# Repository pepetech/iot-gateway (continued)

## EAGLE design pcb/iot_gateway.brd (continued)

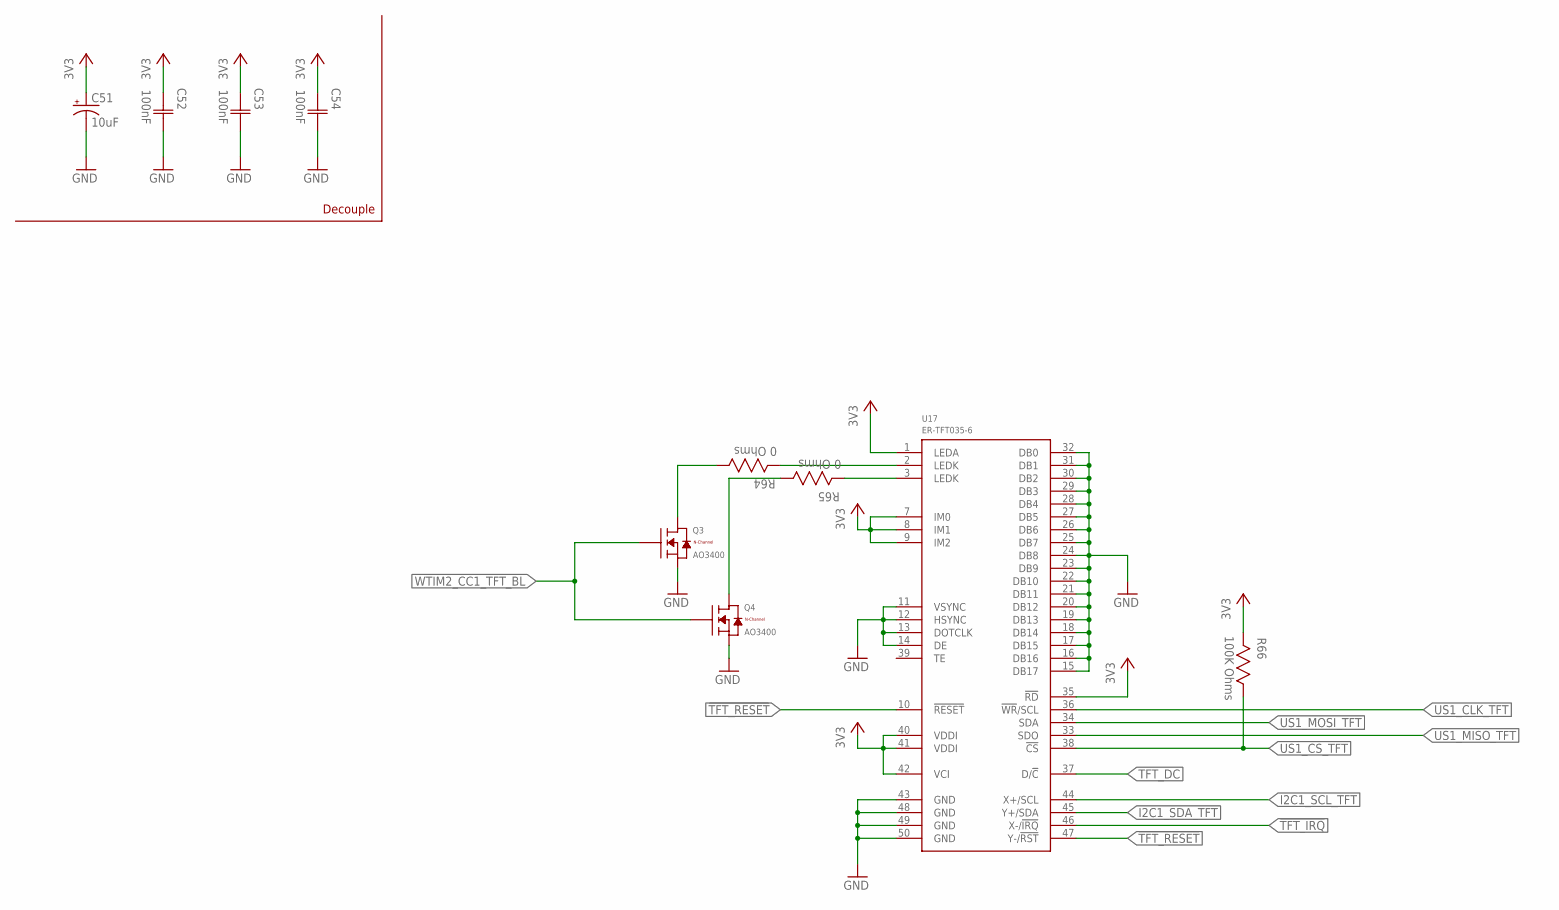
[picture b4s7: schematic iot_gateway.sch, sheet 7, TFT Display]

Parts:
C51: 10uF; TAN-CAP-CASE-A
C52, C53, C54: 100nF; CAP0603
Q3, Q4: AO3400; SOT23
R64, R65: 0 Ohms; RES0603
R66: 100K Ohms; RES0603
U17: ER-TFT035-6; ZIF50

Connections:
3V3: C51.A (+), C52.1 (C1), C53.1 (C1), C54.1 (C1), R66.2, U17.1 (LEDA), U17.7 (IM0), U17.8 (IM1), U17.9 (IM2), U17.35 (!RD), U17.40 (VDDI), U17.41 (VDDI), U17.42 (VCI); also elsewhere on the board
!TFT_IRQ: U17.46 (X-/!IRQ!); also elsewhere on the board
!TFT_RESET: U17.10 (!RESET), U17.47 (Y-/!RST!); also elsewhere on the board
GND: C51.C (-), C52.2 (C2), C53.2 (C2), C54.2 (C2), Q3.2 (S), Q4.2 (S), U17.11 (VSYNC), U17.12 (HSYNC), U17.13 (DOTCLK), U17.14 (DE), U17.15 (DB17), U17.16 (DB16), U17.17 (DB15), U17.18 (DB14), U17.19 (DB13), U17.20 (DB12), U17.21 (DB11), U17.22 (DB10), U17.23 (DB9), U17.24 (DB8), U17.25 (DB7), U17.26 (DB6), U17.27 (DB5), U17.28 (DB4), U17.29 (DB3), U17.30 (DB2), U17.31 (DB1), U17.32 (DB0), U17.43 (GND), U17.48 (GND), U17.49 (GND), U17.50 (GND); also elsewhere on the board
I2C1_SCL_TFT: U17.44 (X+/SCL); also elsewhere on the board
I2C1_SDA_TFT: U17.45 (Y+/SDA); also elsewhere on the board
unnamed: Q3.3 (D), R64.1
unnamed: Q4.3 (D), R65.1
unnamed: R65.2, U17.3 (LEDK)
unnamed: R64.2, U17.2 (LEDK)
TFT_DC: U17.37 (D/!C!); also elsewhere on the board
US1_CLK_TFT: U17.36 (!WR!/SCL); also elsewhere on the board
US1_CS_TFT: R66.1, U17.38 (!CS); also elsewhere on the board
US1_MISO_TFT: U17.33 (SDO); also elsewhere on the board
US1_MOSI_TFT: U17.34 (SDA); also elsewhere on the board
WTIM2_CC1_TFT_BL: Q3.1 (G), Q4.1 (G); also elsewhere on the board

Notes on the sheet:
Decouple

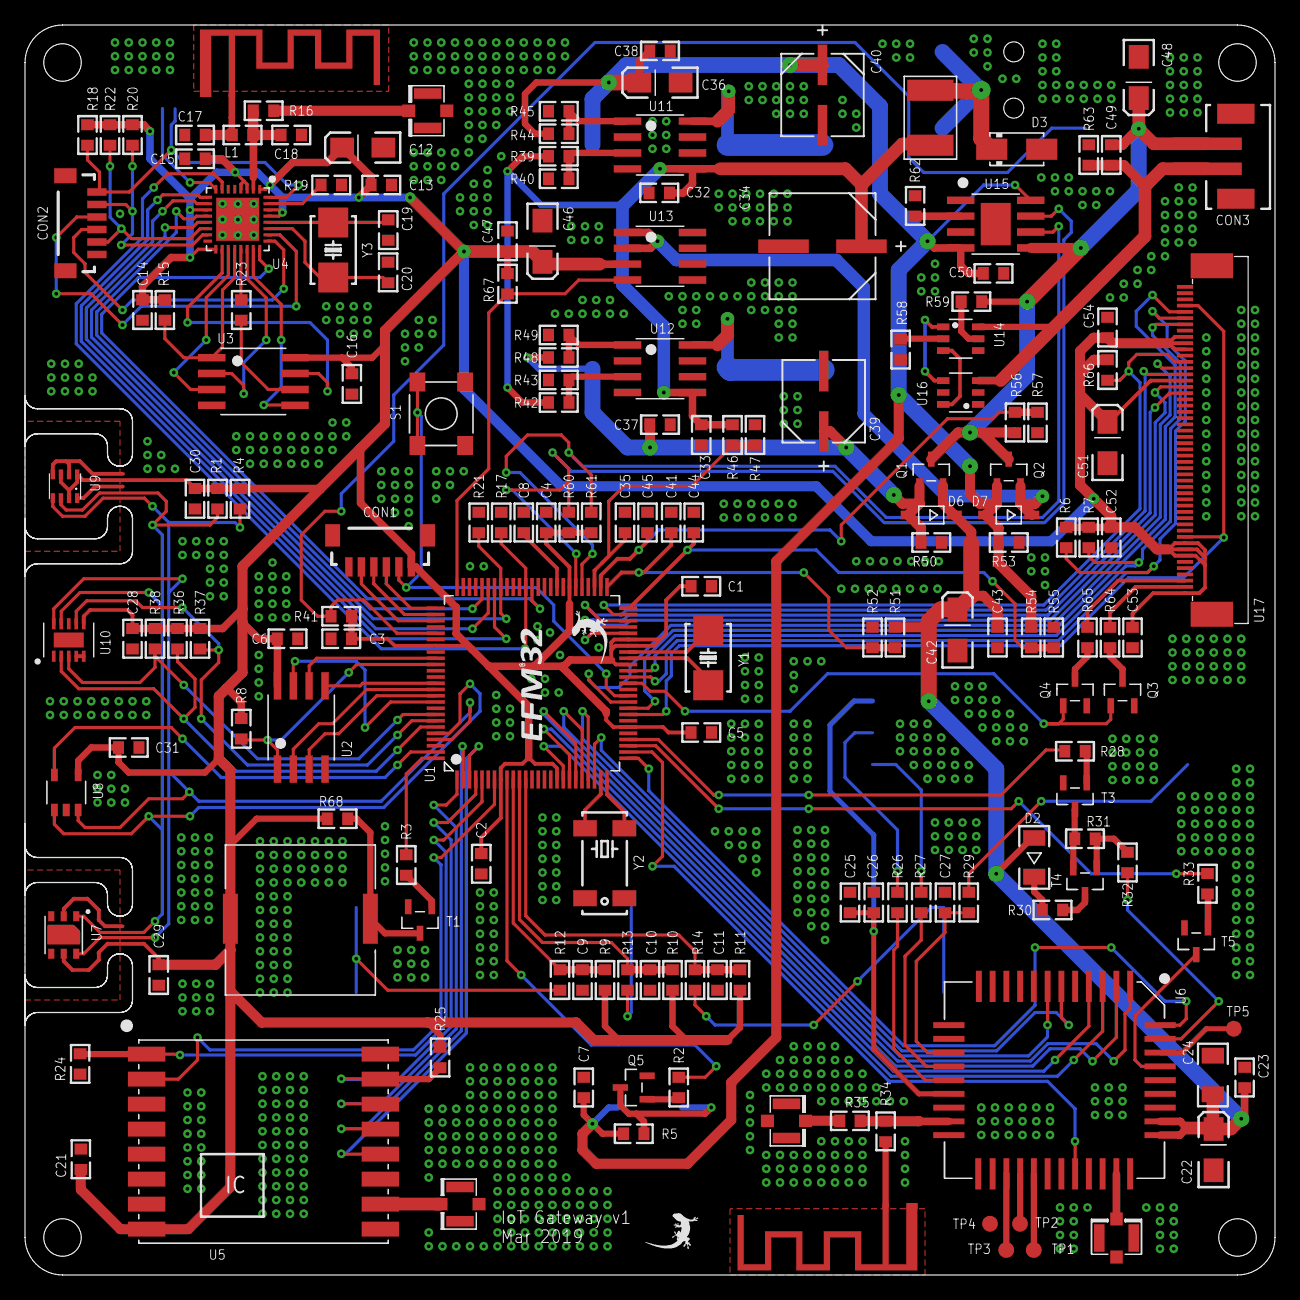
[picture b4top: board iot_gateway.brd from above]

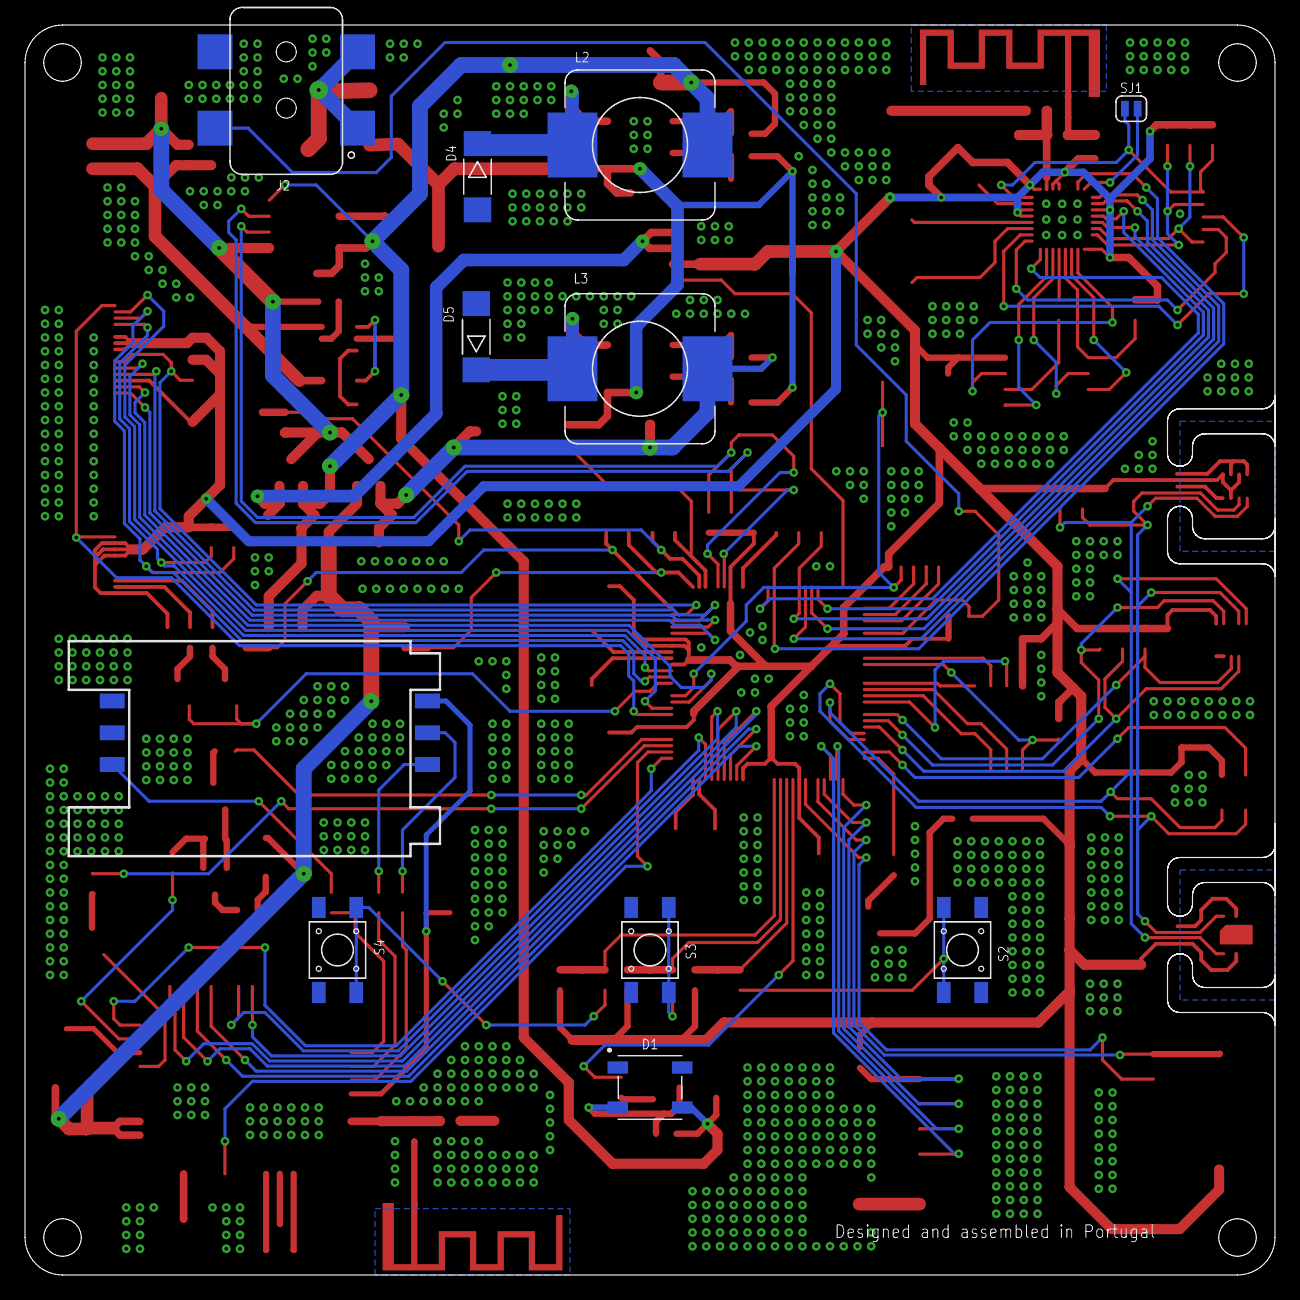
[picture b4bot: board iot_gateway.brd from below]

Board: 2 copper layers, 100.0 x 100.0 mm, 185 parts (11 on the bottom side), 142 nets.

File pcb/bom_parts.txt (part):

Partlist exported from E:/Projetos/ARM/ARMdev/projects/iot-gateway/pcb/iot_gateway.sch at 06/05/2019 23:54

Part   Value              Device                            Package                     Description                                                 
B1     BUZZER-SMD         BUZZER-SMD                        SMD                                                                                     
C1     100nF              CAPACITOR-0603                    CAP0603                                                                                 
C2     100nF              CAPACITOR-0603                    CAP0603                                                                                 
C3     100nF              CAPACITOR-0603                    CAP0603                                                                                 
C4     100nF              CAPACITOR-0603                    CAP0603                                                                                 
C5     100nF              CAPACITOR-0603                    CAP0603                                                                                 
C6     100nF              CAPACITOR-0603                    CAP0603                                                                                 
C7     100nF              CAPACITOR-0603                    CAP0603                                                                                 
C8     1uF                CAPACITOR-0603                    CAP0603                                                                                 
C9     1nF                CAPACITOR-0603                    CAP0603                                                                                 
C10    1nF                CAPACITOR-0603                    CAP0603                                                                                 
C11    1nF                CAPACITOR-0603                    CAP0603                                                                                 
C12    10uF               TANTALUM-CAPACITOR-CASE-A-EIA3216 TAN-CAP-CASE-A                                                                          
C13    100nF              CAPACITOR-0603                    CAP0603                                                                                 
C14    100nF              CAPACITOR-0603                    CAP0603                                                                                 
C15    100nF              CAPACITOR-0603                    CAP0603                                                                                 
C16    100nF              CAPACITOR-0603                    CAP0603                                                                                 
C17    4pF                CAPACITOR-0603                    CAP0603                                                                                 
C18    4.7pF              CAPACITOR-0603                    CAP0603                                                                                 
C19    20pF               CAPACITOR-0603                    CAP0603                                                                                 
C20    20pF               CAPACITOR-0603                    CAP0603                                                                                 
C21    100nF              CAPACITOR-0603                    CAP0603                                                                                 
C22    10uF               TANTALUM-CAPACITOR-CASE-A-EIA3216 TAN-CAP-CASE-A                                                                          
C23    100nF              CAPACITOR-0603                    CAP0603                                                                                 
C24    100uF              CAPACITOR-1206                    CAP1206                                                                                 
C25    1uF                CAPACITOR-0603                    CAP0603                                                                                 
C26    33pF               CAPACITOR-0603                    CAP0603                                                                                 
C27    33pF               CAPACITOR-0603                    CAP0603                                                                                 
C28    100nF              CAPACITOR-0603                    CAP0603                                                                                 
C29    100nF              CAPACITOR-0603                    CAP0603                                                                                 
C30    100nF              CAPACITOR-0603                    CAP0603                                                                                 
C31    100nF              CAPACITOR-0603                    CAP0603                                                                                 
C32    100nF              CAPACITOR-0603                    CAP0603                                                                                 
C33    100nF              CAPACITOR-0603                    CAP0603                                                                                 
C34    470uF              ALUMINIUM-CAPACITOR-CASE-F        AL-CAP-CASE-F                                                                           
C35    470pF              CAPACITOR-0603                    CAP0603                                                                                 
C36    10uF               TANTALUM-CAPACITOR-CASE-A-EIA3216 TAN-CAP-CASE-A                                                                          
C37    100nF              CAPACITOR-0603                    CAP0603                                                                                 
C38    100nF              CAPACITOR-0603                    CAP0603                                                                                 
C39    220uF              ALUMINIUM-CAPACITOR-CASE-D        AL-CAP-CASE-D                                                                           
C40    220uF              ALUMINIUM-CAPACITOR-CASE-D        AL-CAP-CASE-D                                                                           
C41    470pF              CAPACITOR-0603                    CAP0603                                                                                 
C42    10uF               TANTALUM-CAPACITOR-CASE-A-EIA3216 TAN-CAP-CASE-A                                                                          
C43    100nF              CAPACITOR-0603                    CAP0603                                                                                 
C44    470pF              CAPACITOR-0603                    CAP0603                                                                                 
C45    470pF              CAPACITOR-0603                    CAP0603                                                                                 
C46    10uF               TANTALUM-CAPACITOR-CASE-A-EIA3216 TAN-CAP-CASE-A                                                                          
C47    100nF              CAPACITOR-0603                    CAP0603                                                                                 
C48    10uF               TANTALUM-CAPACITOR-CASE-A-EIA3216 TAN-CAP-CASE-A                                                                          
C49    100nF              CAPACITOR-0603                    CAP0603                                                                                 
C50    100nF              CAPACITOR-0603                    CAP0603                                                                                 
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
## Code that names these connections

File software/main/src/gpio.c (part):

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    // Port A
    GPIO->P[0].CTRL   = GPIO_P_CTRL_DRIVESTRENGTHALT_STRONG | (6 << _GPIO_P_CTRL_SLEWRATEALT_SHIFT)
                      | GPIO_P_CTRL_DRIVESTRENGTH_STRONG | (6 << _GPIO_P_CTRL_SLEWRATE_SHIFT);
    GPIO->P[0].MODEL  = GPIO_P_MODEL_MODE0_PUSHPULL                 // US3_MOSI_RFM - Location 0
                      | GPIO_P_MODEL_MODE1_INPUTPULLFILTER          // US3_MISO_RFM - Location 0
                      | GPIO_P_MODEL_MODE2_PUSHPULL                 // US3_CLK_RFM - Location 0
                      | GPIO_P_MODEL_MODE3_PUSHPULL                 // US3_CS_RFM - Location 0
                      | GPIO_P_MODEL_MODE4_PUSHPULL                 // RFM_RESET
                      | GPIO_P_MODEL_MODE5_DISABLED                 // NR
                      | GPIO_P_MODEL_MODE6_INPUTPULLFILTER          // RFM_IRQ
                      | GPIO_P_MODEL_MODE7_INPUTPULLFILTER;         // GSM_STATUS
    GPIO->P[0].MODEH  = GPIO_P_MODEH_MODE8_INPUTPULLFILTER          // GSM_RF_SYNC
                      | GPIO_P_MODEH_MODE9_PUSHPULL                 // GSM_PWR_KEY
                      | GPIO_P_MODEH_MODE10_PUSHPULL                // GSM_LED_EN
                      | GPIO_P_MODEH_MODE11_DISABLED                // NR
                      | GPIO_P_MODEH_MODE12_PUSHPULL                // TFT_RESET
                      | GPIO_P_MODEH_MODE13_INPUTPULLFILTER         // TFT_IRQ
                      | GPIO_P_MODEH_MODE14_PUSHPULL                // TFT_DC
                      | GPIO_P_MODEH_MODE15_PUSHPULL;               // TIM3_CC2_BUZZ - Location 0
    GPIO->P[0].DOUT   = BIT(3) | BIT(10) | BIT(12) | BIT(13);
    GPIO->P[0].OVTDIS = 0;

    // Port B
    GPIO->P[1].CTRL   = GPIO_P_CTRL_DRIVESTRENGTHALT_STRONG | (6 << _GPIO_P_CTRL_SLEWRATEALT_SHIFT)
                      | GPIO_P_CTRL_DRIVESTRENGTH_STRONG | (6 << _GPIO_P_CTRL_SLEWRATE_SHIFT);
    GPIO->P[1].MODEL  = GPIO_P_MODEL_MODE0_PUSHPULL                 // LED_DI
                      | GPIO_P_MODEL_MODE1_INPUTPULLFILTER          // BTN_1
                      | GPIO_P_MODEL_MODE2_INPUTPULLFILTER          // BTN_2
                      | GPIO_P_MODEL_MODE3_INPUTPULLFILTER          // BTN_3
                      | GPIO_P_MODEL_MODE4_DISABLED                 // NR
                      | GPIO_P_MODEL_MODE5_DISABLED                 // NR
                      | GPIO_P_MODEL_MODE6_DISABLED                 // NR
                      | GPIO_P_MODEL_MODE7_DISABLED;                // MAIN_LFXTAL_P
    GPIO->P[1].MODEH  = GPIO_P_MODEH_MODE8_DISABLED                 // MAIN_LFXTAL_N
                      | GPIO_P_MODEH_MODE9_DISABLED                 // NR
                      | GPIO_P_MODEH_MODE10_PUSHPULL                // WTIM2_CC1_TFT_BL - Location 2
                      | GPIO_P_MODEH_MODE11_WIREDANDPULLUPFILTER    // I2C1_SDA_TFT - Location 1
                      | GPIO_P_MODEH_MODE12_WIREDANDPULLUPFILTER    // I2C1_SCL_TFT - Location 1
                      | GPIO_P_MODEH_MODE13_DISABLED                // MAIN_HFXTAL_P
                      | GPIO_P_MODEH_MODE14_DISABLED                // MAIN_HFXTAL_N
                      | GPIO_P_MODEH_MODE15_DISABLED;               // NC
    GPIO->P[1].DOUT   = BIT(0) | BIT(1) | BIT(2) | BIT(3);
    GPIO->P[1].OVTDIS = 0;
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    // Port C
    GPIO->P[2].CTRL   = GPIO_P_CTRL_DRIVESTRENGTHALT_STRONG | (6 << _GPIO_P_CTRL_SLEWRATEALT_SHIFT)
                      | GPIO_P_CTRL_DRIVESTRENGTH_STRONG | (7 << _GPIO_P_CTRL_SLEWRATE_SHIFT);
    GPIO->P[2].MODEL  = GPIO_P_MODEL_MODE0_PUSHPULL                 // US2_RTS_GSM - Location 0
                      | GPIO_P_MODEL_MODE1_INPUTPULLFILTER          // US2_CTS_GSM - Location 0
                      | GPIO_P_MODEL_MODE2_PUSHPULL                 // US2_TX_GSM - Location 0
                      | GPIO_P_MODEL_MODE3_INPUTPULLFILTER          // US2_RX_GSM - Location 0
                      | GPIO_P_MODEL_MODE4_INPUTPULLFILTER          // GSM_RING
                      | GPIO_P_MODEL_MODE5_PUSHPULL                 // GSM_DTR
                      | GPIO_P_MODEL_MODE6_INPUTPULLFILTER          // BAT_STDBY
                      | GPIO_P_MODEL_MODE7_INPUTPULLFILTER;         // BAT_CHRG
    GPIO->P[2].MODEH  = GPIO_P_MODEH_MODE8_PUSHPULL                 // US0_CS_WIFI - Location 2
                      | GPIO_P_MODEH_MODE9_PUSHPULL                 // US0_CLK_WIFI - Location 2
                      | GPIO_P_MODEH_MODE10_INPUTPULLFILTER         // US0_MISO_WIFI - Location 2
                      | GPIO_P_MODEH_MODE11_PUSHPULL                // US0_MOSI_WIFI - Location 2
                      | GPIO_P_MODEH_MODE12_DISABLED                // NC
                      | GPIO_P_MODEH_MODE13_DISABLED                // NC
                      | GPIO_P_MODEH_MODE14_DISABLED                // NC
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    // Port D
    GPIO->P[3].CTRL   = GPIO_P_CTRL_DRIVESTRENGTHALT_STRONG | (6 << _GPIO_P_CTRL_SLEWRATEALT_SHIFT)
                      | GPIO_P_CTRL_DRIVESTRENGTH_STRONG | (6 << _GPIO_P_CTRL_SLEWRATE_SHIFT);
    GPIO->P[3].MODEL  = GPIO_P_MODEL_MODE0_PUSHPULL                 // US1_MOSI_TFT - Location 1
                      | GPIO_P_MODEL_MODE1_INPUTPULLFILTER          // US1_MISO_TFT - Location 1
                      | GPIO_P_MODEL_MODE2_PUSHPULL                 // US1_CLK_TFT - Location 1
                      | GPIO_P_MODEL_MODE3_PUSHPULL                 // US1_CS_TFT - Location 1
                      | GPIO_P_MODEL_MODE4_DISABLED                 // 5V0_SENSE
                      | GPIO_P_MODEL_MODE5_DISABLED                 // 4V2_SENSE
                      | GPIO_P_MODEL_MODE6_DISABLED                 // VBAT_SENSE
                      | GPIO_P_MODEL_MODE7_DISABLED;                // VIN_SENSE
    GPIO->P[3].MODEH  = GPIO_P_MODEH_MODE8_DISABLED                 // NR
                      | GPIO_P_MODEH_MODE9_PUSHPULL                 // QSPI0_DQ0 - Location 0
                      | GPIO_P_MODEH_MODE10_PUSHPULL                // QSPI0_DQ1 - Location 0
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    GPIO->P[4].MODEL  = GPIO_P_MODEL_MODE0_DISABLED                 // NR
                      | GPIO_P_MODEL_MODE1_DISABLED                 // NR
                      | GPIO_P_MODEL_MODE2_DISABLED                 // NR
                      | GPIO_P_MODEL_MODE3_INPUTPULLFILTER          // WIFI_IRQ
                      | GPIO_P_MODEL_MODE4_PUSHPULL                 // WIFI_EN
                      | GPIO_P_MODEL_MODE5_DISABLED                 // NR
                      | GPIO_P_MODEL_MODE6_DISABLED                 // NR
                      | GPIO_P_MODEL_MODE7_DISABLED;                // NR
    GPIO->P[4].MODEH  = GPIO_P_MODEH_MODE8_DISABLED                 // NR
                      | GPIO_P_MODEH_MODE9_INPUTPULLFILTER          // CCS811_IRQ
                      | GPIO_P_MODEH_MODE10_PUSHPULL                // CCS811_WAKE
                      | GPIO_P_MODEH_MODE11_PUSHPULL                // CCS811_RESET
                      | GPIO_P_MODEH_MODE12_WIREDANDPULLUPFILTER    // I2C0_SDA_SENS - Location 6
                      | GPIO_P_MODEH_MODE13_WIREDANDPULLUPFILTER    // I2C0_SCL_SENS - Location 6
                      | GPIO_P_MODEH_MODE14_DISABLED                // NR
                      | GPIO_P_MODEH_MODE15_INPUTPULLFILTER;        // MAG_ALERT
    GPIO->P[4].DOUT   = BIT(9) | BIT(10) | BIT(11);
    GPIO->P[4].OVTDIS = 0;

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    GPIO->P[5].MODEH  = GPIO_P_MODEH_MODE8_DISABLED                 // NR
                      | GPIO_P_MODEH_MODE9_DISABLED                 // NR
                      | GPIO_P_MODEH_MODE10_DISABLED                // NR
                      | GPIO_P_MODEH_MODE11_INPUTPULLFILTER         // VREG_ERR
                      | GPIO_P_MODEH_MODE12_DISABLED                // VIN_DET - FIXME: Hardware fix needed
                      | GPIO_P_MODEH_MODE13_DISABLED                // NC
                      | GPIO_P_MODEH_MODE14_DISABLED                // NC
                      | GPIO_P_MODEH_MODE15_DISABLED;               // NC
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
    // Debugger Route
    GPIO->ROUTEPEN &= ~(GPIO_ROUTEPEN_TDIPEN | GPIO_ROUTEPEN_TDOPEN);   // Disable JTAG
    GPIO->ROUTEPEN |= GPIO_ROUTEPEN_SWVPEN;                             // Enable SWO
    GPIO->ROUTELOC0 = GPIO_ROUTELOC0_SWVLOC_LOC0;                       // SWO on PF2

    // External interrupts
    GPIO->EXTIPSELL = GPIO_EXTIPSELL_EXTIPSEL0_PORTE            // WIFI_IRQ
                    | GPIO_EXTIPSELL_EXTIPSEL1_PORTB            // BTN_1
                    | GPIO_EXTIPSELL_EXTIPSEL2_PORTB            // BTN_2
                    | GPIO_EXTIPSELL_EXTIPSEL3_PORTB            // BTN_3
                    | GPIO_EXTIPSELL_EXTIPSEL4_PORTA            // RFM_IRQ
                    | GPIO_EXTIPSELL_EXTIPSEL5_PORTA            // GSM_STATUS
                    | GPIO_EXTIPSELL_EXTIPSEL6_PORTC            // GSM_RING
                    | GPIO_EXTIPSELL_EXTIPSEL7_PORTC;           // BAT_CHRG
    GPIO->EXTIPSELH = GPIO_EXTIPSELH_EXTIPSEL8_PORTA            // GSM_RF_SYNC
                    | GPIO_EXTIPSELH_EXTIPSEL9_PORTE            // CCS811_IRQ
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
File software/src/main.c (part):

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    fDVDDHighThresh = fDVDDLowThresh + 0.026f; // Hysteresis from datasheet
    fIOVDDHighThresh = fIOVDDLowThresh + 0.026f; // Hysteresis from datasheet

    usart0_init(18000000, 0, USART_SPI_MSB_FIRST, 2, 2, 2);  // SPI0 at 18MHz on Location 2 MISO:PC10 MOSI:PC11 CLK:PC9 ESP8266 WIFI-COPROCESSOR
    usart1_init(18000000, 0, USART_SPI_MSB_FIRST, 1, 1, 1);  // SPI1 at 18MHz on Location 1 MISO:PD1 MOSI:PD0 CLK:PD2 ILI9488 Display
    //usart2_init(115200, 0, UART_FRAME_STOPBITS_ONE, 0, 0, 0); // USART2 at 115200Baud on Location 0 RTS-PC0 CTS-PC1 TX-PC2 RX-PC3 GSM
    //usart3_init(10000000, 0, USART_SPI_MSB_FIRST, 0, 0, 0); // SPI3 at 10MHz on Location 0 MISO-PA1 MOSI-PA0 CLK-PA2 RFM

    i2c0_init(I2C_NORMAL, 6, 6); // Init I2C0 at 100 kHz on location 6 SCL:SDA PE13:PE12 Sensors
    i2c1_init(I2C_NORMAL, 1, 1); // Init I2C1 at 100 kHz on location 1 SCL:SDA PB12:PB11 TFT Touch Controller

    char szDeviceName[32];

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
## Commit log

2019-03-24 Change libs to new scheme
2019-03-24 Fix typo in library name
2019-03-25 Update libraries
2019-03-26 Final board ordered
2019-03-27 Add .gitignore to PCB files
2019-03-30 Change gateway sch frame
2019-04-15 added files in preparation for software development, cloned from gecko-dev
2019-04-15 code gpio labelling
2019-04-16 gpio initial configuration, macros for gpio manipulation
2019-04-16 pin defaults corrections
2019-04-16 Add LFXO
2019-04-16 added display driver
2019-04-16 forgot to git add
2019-04-16 tft display tests
2019-04-16 Add Pepe and Landscape photos
2019-04-16 Add backlight PWM. Add print of battery status
2019-04-16 Add buzzer
2019-04-16 Change pepe to 64x64
2019-04-16 Changed patrick
2019-04-16 bugfixing ili9488
2019-04-16 more pepe
2019-04-16 Add wifi coprocessor app Add wifi coprocessor bootloader Organize software folder
2019-04-17 added a nice surprise
2019-04-17 Setup wifi coprocessor app to compile
2019-04-17 added font support for display
2019-04-17 Organize things
2019-04-17 Remove wifi unused code Wifi scanning works
2019-04-17 display terminal experimentation
2019-04-17 experimental textbox feature
2019-04-18 Add SPI slave Added IO configuration Added new register bits
2019-04-18 experimental terminal
2019-04-19 unclean but working tft terminal, needs refactoring
2019-04-19 Refactor and organize TFT display code Add BMP280 library
2019-04-19 Remove old information from QSPI
2019-04-19 Organize GPIO comments Add power rail measurements
2019-04-19 Add unknown bit in wifi registers
2019-04-20 Work on wifi SPI slave
2019-04-20 Experiment with OPAMP + ACMP to monitor battery
2019-04-20 More ACMP work Add external interrupts
2019-04-20 Forgot to add mask on gpio ISRs
2019-04-21 added tft graph drawing code
2019-04-21 removed tft header leftover and unintended bin folder
2019-04-21 Typo fixes Added USART DMA (needs testing)
2019-04-21 Forgot to switch USART back to SPI mode
2019-04-21 Remove the last "delay_ms(10);" accidentally pasted
2019-04-21 Added human readable sizes option to makefile
2019-04-21 Added human readable sizes option to wifi makefile
2019-04-21 Fix typos and semantics
2019-04-22 minor random changes
2019-04-22 Remove ACMP1 flags clear Bus fault was caused because the clock to the module is disabled
2019-04-24 Random changes and typo fixes
2019-04-24 Disable RAM prefetching to fix BME Usage Faults Change SVD file to 420
2019-04-25 Use I2C macros Add CCS811 header Add SI7021 header
2019-04-25 Add WS2812B library (needs testing) Added functions to LDMA library
2019-04-25 Changes in WS2812B library, but still no success
2019-04-26 USART works WS2812B works
2019-04-26 Compatibility changes to WS2812B library Add RFM69 Add all the USARTs
2019-04-27 Add RMU Disable LFXO before configuring Disable VMONs before configuring
2019-04-28 Add CCS811 library
2019-04-28 Add SI7021 (needs testing)
2019-04-29 Tested SI1145 Fixed RMU library
2019-04-29 Random changes
2019-04-29 minor graph changes
2019-04-30 added driver for the tft touch controller
2019-04-30 added multiprocessing support to makefile
2019-04-30 tiny ups
2019-04-30 makefile corrections
2019-04-30 touch controller tests
2019-04-30 Fix WS2812 and FT6x36
2019-04-30 i2c bugfixing
2019-04-30 graph capping
2019-04-30 Wifi coprocessor changes
2019-05-03 display button funcionality
2019-05-03 display draw button minor fix
2019-05-03 implemented SI7210
    implemented SI7210
    implemented SI7210
    implemented SI7210
    implemented SI7210
    sync
2019-05-06 Fix hardware errors
2019-05-06 Add most recent gerbers
2019-05-07 Added eagle project file
2019-05-10 i always forgetti
2019-05-30 Fix typos and enable Flash prefetching
2019-05-30 Add output HEX for userdata section
2019-05-30 Allow DCDC 0 mA reverse current
2019-07-09 Fix bug in RFM69 library
2019-07-24 Fix library paths
2019-07-28 Sync RFM69 settings
2019-08-02 Tweak WS2812 lib
2019-08-05 Zero variables before i2c read
2019-08-05 Huge code rework Changed ILI9488 read id function, needs testing All code needs testing
2019-08-19 Changes to QSPI library (tested with W25Q32, needs testing with actual flash used SST26VF064B)
2019-09-09 Fix bug with DCDC init function
2019-12-14 Small change according to ESP8266 register documentation
2019-12-14 Start schematic redesign
2019-12-27 Big changes to main schematic Finished USB/PD daughter board
2019-12-28 Place everything important inside the board space and start routing
2019-12-28 Add case 3D models
2019-12-28 Connect IOs to MCU
2019-12-31 Update libraries Finish routing Generate schematic PDF files
2020-01-01 Start machine gun process
2020-01-02 Maybe finished?
2020-02-03 Fix ADC precision loss by right shift instead of dividing (already fixed before but came back?)
2020-02-06 Update get_free_ram with a more precise version
2020-03-07 Change 5V_NBU regulator to LT8640S
2020-08-31 Sync
2021-02-01 Fix ADC stuck in low accuracy bias mode Update GCC and CMSIS
2021-02-05 Prevent compiller from optimizing startup RAM data copy
2021-02-05 Add gerber files for production
